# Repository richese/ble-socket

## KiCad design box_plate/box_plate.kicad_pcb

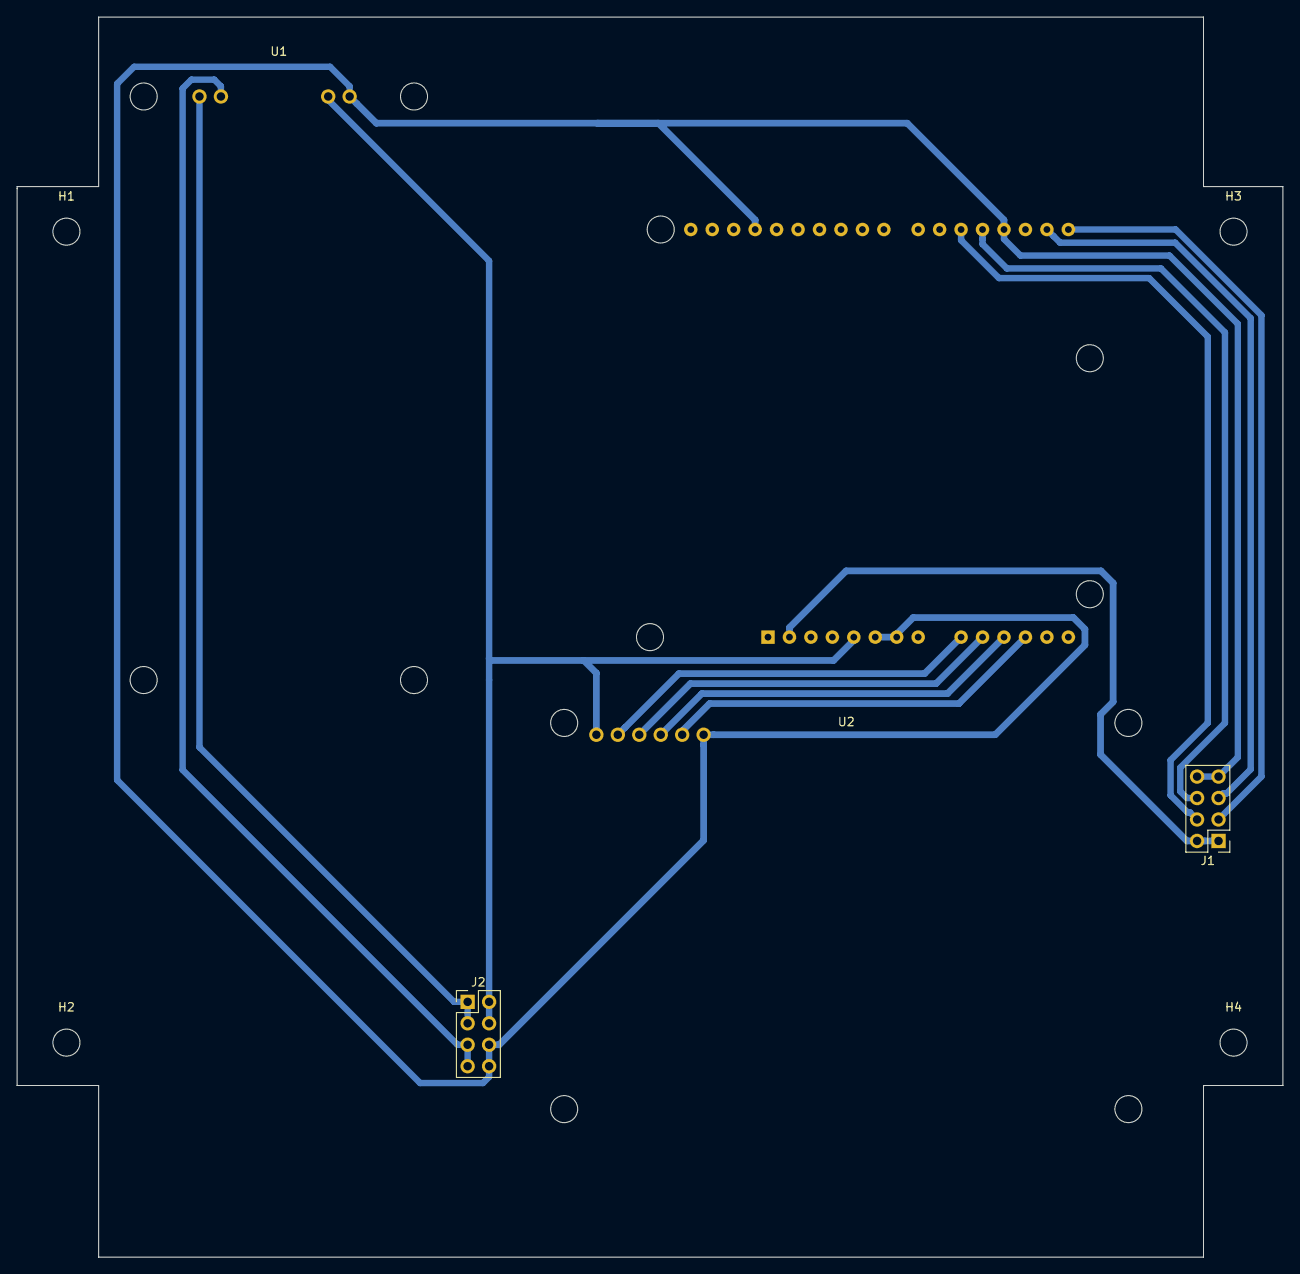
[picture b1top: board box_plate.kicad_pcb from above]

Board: 2 copper layers, 149.9 x 146.8 mm, 9 parts (1 on the bottom side), 13 nets.

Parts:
H1, H2, H3, H4: MountingHole; MountingHole_3.2mm_M3
J1, J2: Conn_02x04_Odd_Even; PinHeader_2x04_P2.54mm_Vertical
U1: PWR_ACDC
U2: RELAY_4CH
U3: RSL10_EVK; Arduino_UNO_R3_WithMountingHoles

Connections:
+3V3: J1.1, J1.2, U3.2
+5V: J2.2, J2.4, U1.1, U2.1, U3.5
+12V: J2.1, J2.3, U1.3
/DIO0: U2.2, U3.9
/DIO1: U2.3, U3.10
/DIO2: U2.4, U3.11
/DIO3: U2.5, U3.12
/DIO4: J1.3, U3.15
/DIO5: J1.5, U3.16
/DIO13: J1.6, U3.19
/DIO14: J1.4, U3.20
GND: J1.7, J1.8, J2.6, J2.8, U1.2, U2.6, U3.6, U3.7, U3.18, U3.29
GNDA: J2.5, J2.7, U1.4

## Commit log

2019-05-21 Initial box plate PCB design.
2019-05-22 Updated PCB files.
2019-06-10 Initial version of switch box firmware
2019-12-04 Started design of v2 board with less pre-build modules.
2019-12-04 Removed transistors that might not be needed.
2019-12-06 Added 12V to 3V3 converter.
